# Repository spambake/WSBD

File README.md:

# WSBD
World's Smallest Bat Detector

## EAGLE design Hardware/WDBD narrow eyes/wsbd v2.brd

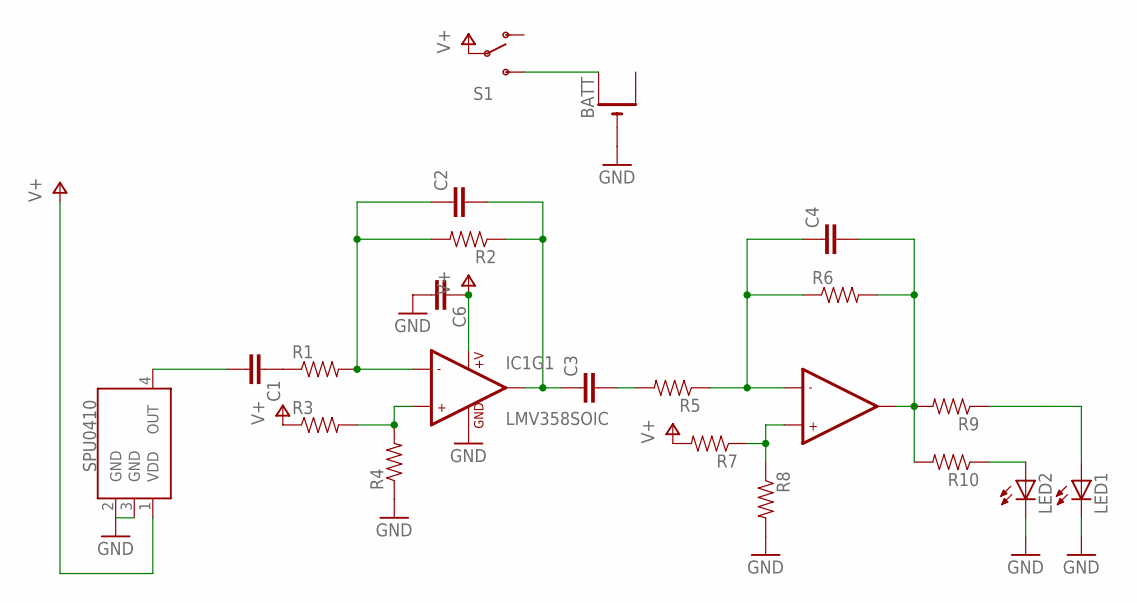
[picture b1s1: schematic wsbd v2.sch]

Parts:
BATT: CR2032MPD1; CR2032-THRU
C1, C2, C3, C4, C6: CAP0805; 0805
IC1: LMV358SOIC; SO08
LED1, LED2: LEDCHIP-LED0805; CHIP-LED0805
R1, R2, R3, R4, R5, R6, R7, R8, R9, R10: RESISTOR0805-RES; 0805
S1: SWITCH-SPDT-SMD-A; SWITCH-SPST-SMD-A
U$1: SPU0410; SPSERIES1

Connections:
GND: BATT.GND (-), C6.2, IC1.4 (GND), LED1.C, LED2.C, R4.1, R8.2, U$1.2 (GND), U$1.3 (GND)
unnamed: C3.2, R5.2
unnamed: C1.1, R1.1
unnamed: C2.1, IC1.2 (-IN1), R1.2, R2.2
unnamed: IC1.3 (+IN1), R3.2, R4.2
unnamed: C2.2, C3.1, IC1.1 (OUT1), R2.1
unnamed: BATT.+1 (+), S1.3 (S)
unnamed: IC1.5 (+IN2), R7.1, R8.1
unnamed: C4.1, IC1.6 (-IN2), R5.1, R6.1
unnamed: C1.2, U$1.4 (OUT)
unnamed: LED1.A, R9.1
unnamed: LED2.A, R10.1
unnamed: C4.2, IC1.7 (OUT2), R6.2, R9.2, R10.2
V+: C6.1, IC1.8 (+V), R3.1, R7.2, S1.2, U$1.1 (VDD)

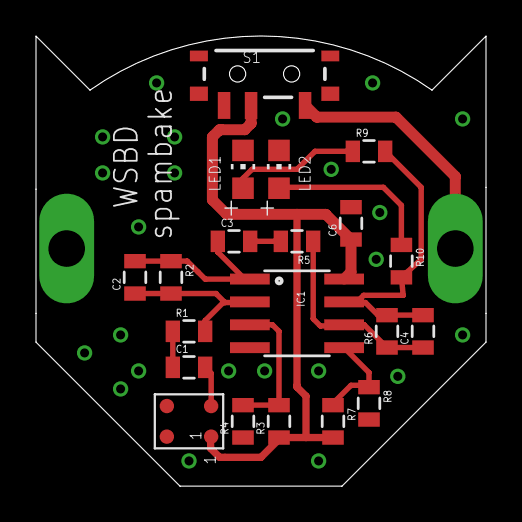
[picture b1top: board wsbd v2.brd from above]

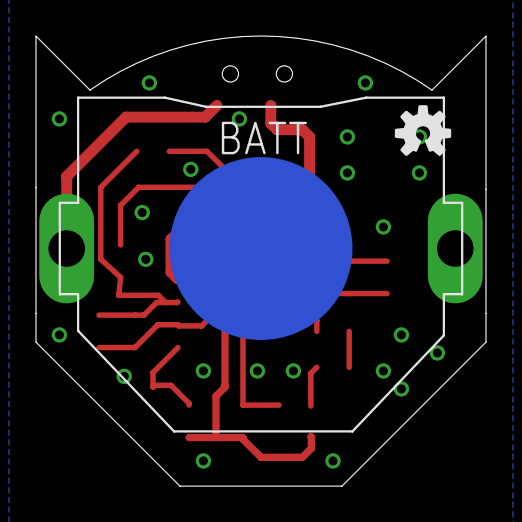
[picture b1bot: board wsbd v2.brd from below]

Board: 2 copper layers, 25.0 x 25.0 mm, 22 parts (2 on the bottom side), 14 nets.

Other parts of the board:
U$2: OSHW-LOGO-S

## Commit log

2015-11-30 Update LICENSE
2015-11-30 Add sch, brd and gerbers for wide eyes
2015-12-01 Add gerbers, brd and sch files for narrow eye version

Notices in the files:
parts and their libraries:
SparkFun-AnalogIC: Licensing:Creative Commons ShareAlike 4.0 International - https://creativecommons.org/licenses/by-sa/4.0
